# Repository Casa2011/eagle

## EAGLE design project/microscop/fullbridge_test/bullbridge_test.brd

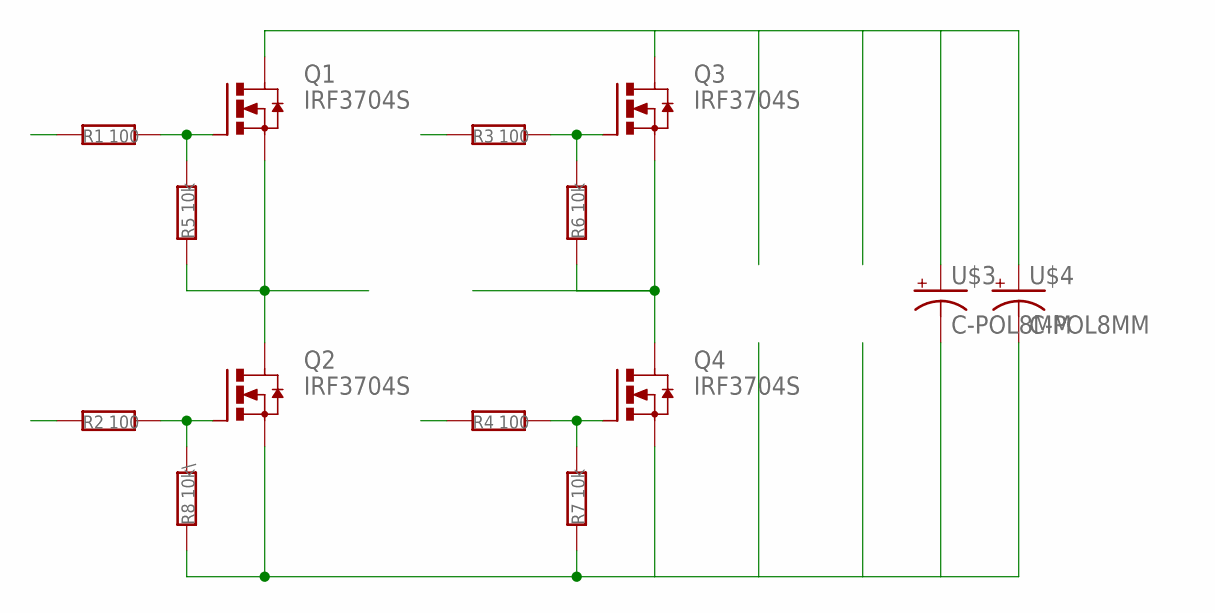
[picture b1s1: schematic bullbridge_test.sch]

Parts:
Q1, Q2, Q3, Q4: IRF3704S; D2PACK
R1, R2, R3, R4: 100; R0805
R5, R6, R7: 10k; R0805
R8: 10k\; R0805
U$3, U$4: C-POL8MM; PCAP8

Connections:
unnamed: Q1.1 (G), R1.2, R5.2
unnamed: Q3.1 (G), R3.2, R6.2
unnamed: Q4.1 (G), R4.2, R7.2
unnamed: Q1.3 (S), Q2.2 (D), R5.1
unnamed: Q3.3 (S), Q4.2 (D), R6.1
unnamed: Q1.2 (D), Q3.2 (D), U$3.P$1 (+), U$4.P$1 (+)
unnamed: Q2.1 (G), R2.2, R8.2
unnamed: Q2.3 (S), Q4.3 (S), R7.1, R8.1, U$3.P$2 (-), U$4.P$2 (-)

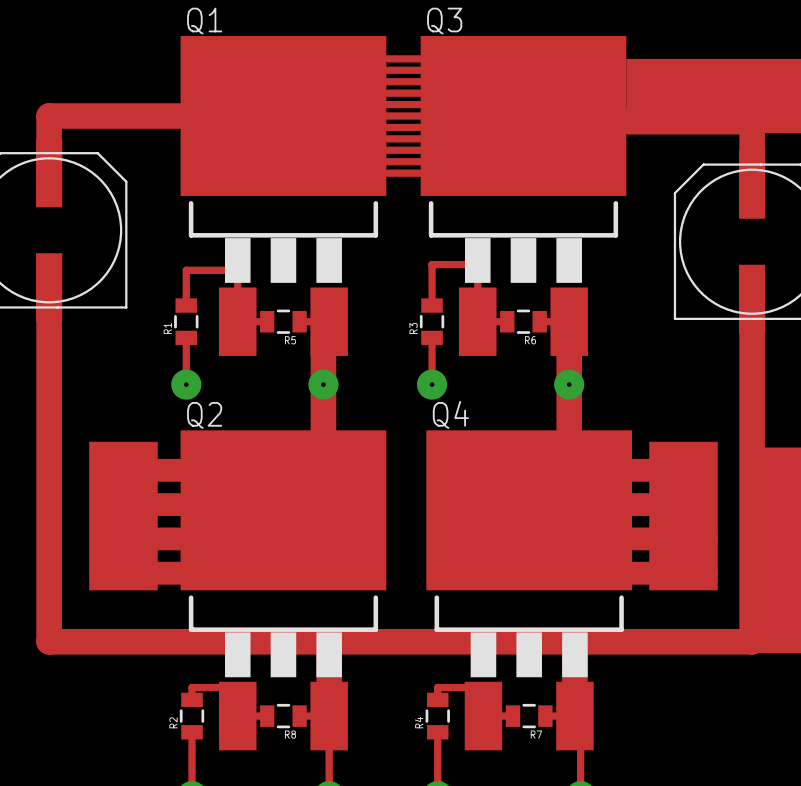
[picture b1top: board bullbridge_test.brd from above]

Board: 2 copper layers, 14 parts (0 on the bottom side), 8 nets.

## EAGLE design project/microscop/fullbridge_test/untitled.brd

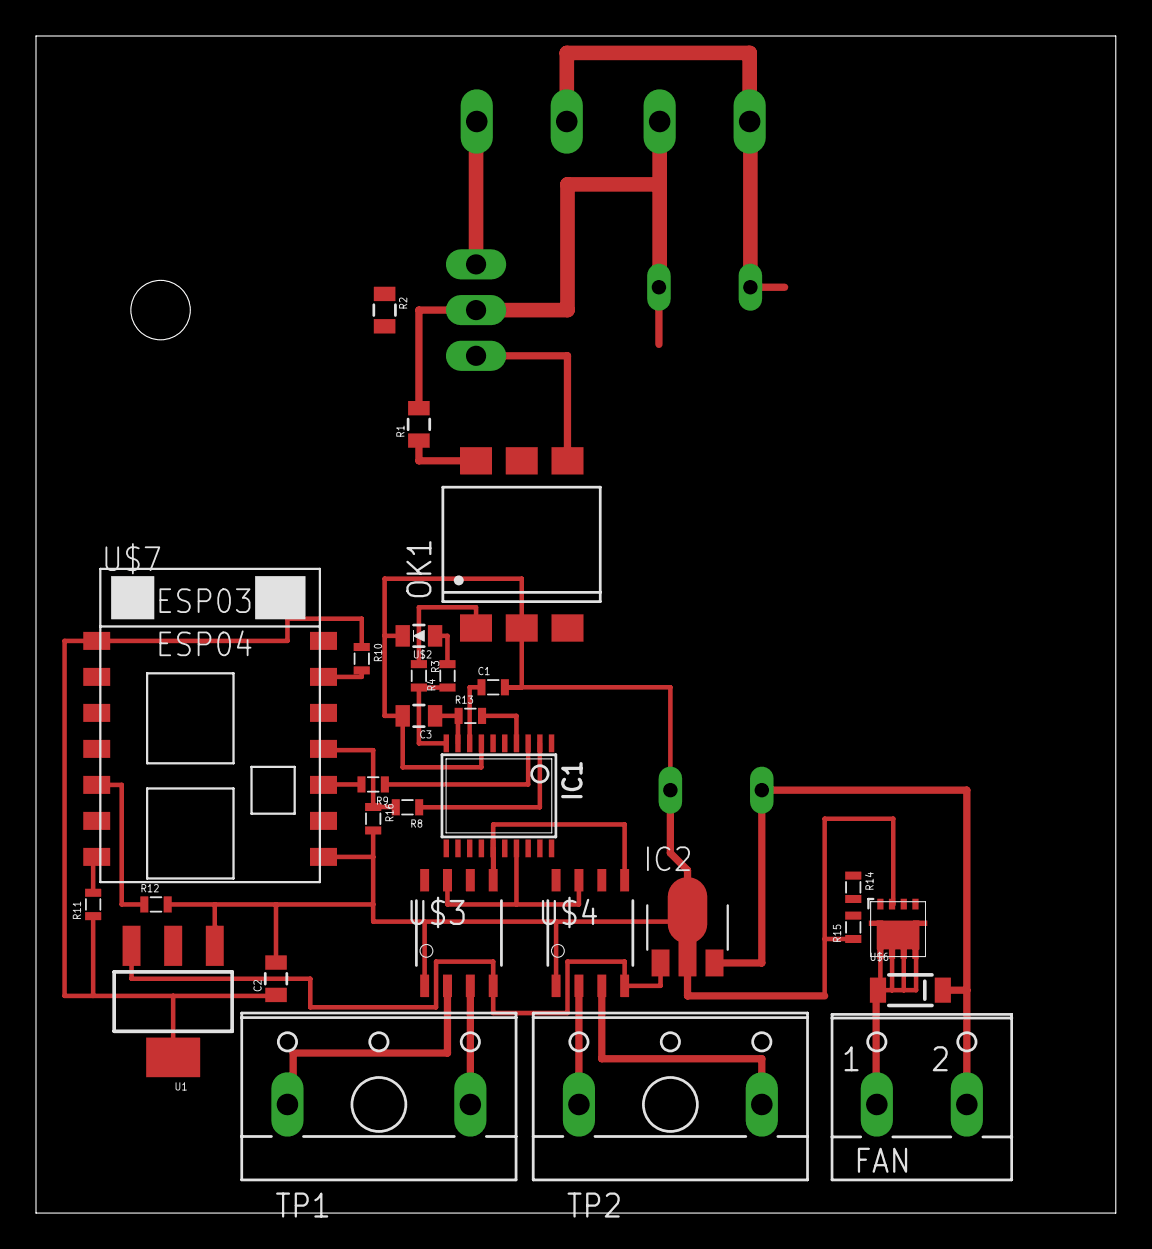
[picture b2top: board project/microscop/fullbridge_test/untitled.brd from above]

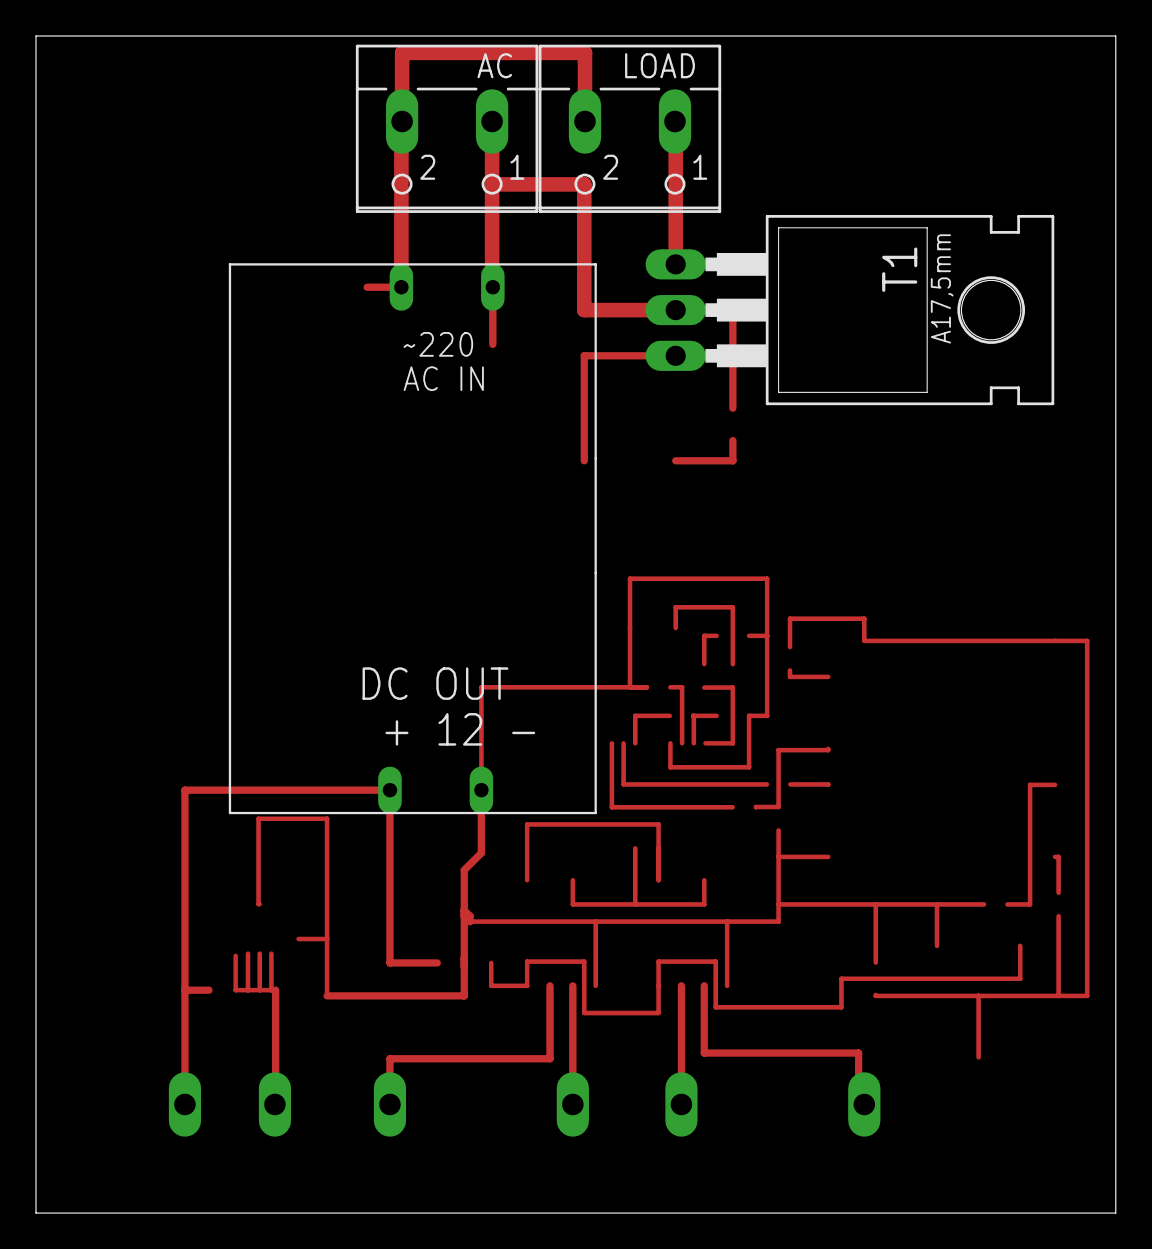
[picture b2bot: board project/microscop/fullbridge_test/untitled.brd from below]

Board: 2 copper layers, 60.0 x 65.4 mm, 33 parts (4 on the bottom side), 29 nets.

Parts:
AC: W237-102
C1: C0603
C2, C3: C0805
FAN: W237-102
IC1: STM8S003F3; TSSOP20
IC2: 78L05F; SOT89
LOAD: W237-102
OK1: MOC3043S; DIL6-SMD
R1, R2: 360; R0805
R3, R4: 1k; 0603
R8, R9, R10, R11, R12, R13, R14, R15, R16: 0603
T1: BT138-H; TO220BH
TP1, TP2: W237-2N
U1: SOT223
U$2: LED0805; 0805-LED
U$3, U$4: MAX6675; SO08
U$5: AON7200; DFN3X3
U$6: PMLL4150; SOD80C
U$7: ESP8266; ESP-03
U$8: AC-DC; ACDC12(1)

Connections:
12V: FAN.2, IC2.3, U$6.C, U$8.+12
+3V3: C2.1, R10.1, R11.1, U1.4, U$7.VCC
+5V: C3.1, IC1.9, IC2.1, R13.1, U1.3, U$3.4, U$4.4
DIMM_IN: IC1.10, R3.2, R4.1
ESP8266_!RST: R10.2, U$7.CH_PD
ESP8266_FLASH: R11.2, U$7.GPIO0
ESP8266_RX: IC1.2, R8.1
ESP8266_TX: IC1.3, R9.1
GND: C1.2, C2.2, C3.2, IC1.7, IC2.2, IC2.2@1, OK1.2, R12.2, R15.1, R16.2, U1.1, U$2.C, U$3.1, U$4.1, U$5.S:1, U$5.S:2, U$5.S:3, U$7.GND, U$8.GND
MAX7765_CLK: IC1.15, U$3.5, U$4.5
MAX7765_OUT: IC1.17, U$3.7, U$4.7
unnamed: TP1.2, U$3.3
unnamed: OK1.1, R3.1
unnamed: R4.2, U$2.A
unnamed: OK1.4, R2.2, T1.G
unnamed: OK1.6, R1.1
unnamed: AC.1, R1.2, T1.T2, U$8.P
unnamed: TP1.1, U$3.2
unnamed: AC.2, LOAD.2, U$8.N
unnamed: LOAD.1, R2.1, T1.T1
unnamed: TP2.2, U$4.3
unnamed: TP2.1, U$4.2
unnamed: R14.2, R15.2, U$5.G
unnamed: R8.2, R16.1, U$7.URXD
unnamed: R9.2, U$7.UTXD
unnamed: R12.1, U$7.GPIO15
unnamed: FAN.1, U$5.D, U$5.D:1, U$5.D:2, U$5.D:3, U$5.D:4, U$5.D:5, U$5.D:6, U$6.A
unnamed: C1.1, IC1.8
STM8_!RST: IC1.4, R13.2

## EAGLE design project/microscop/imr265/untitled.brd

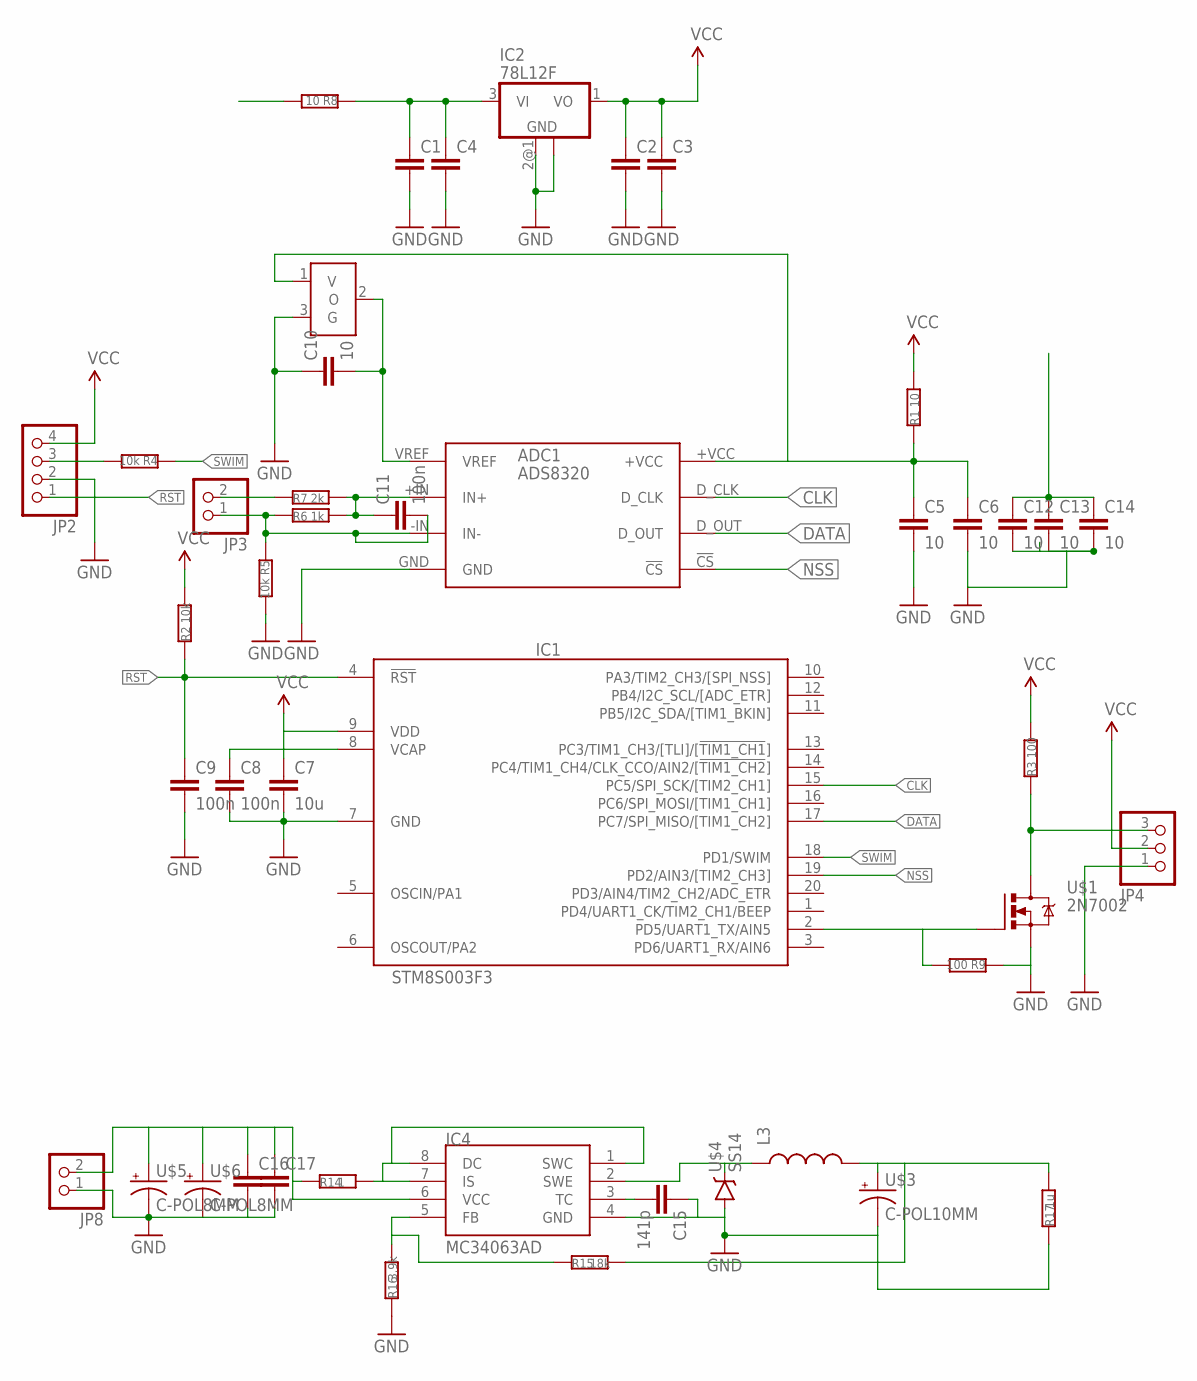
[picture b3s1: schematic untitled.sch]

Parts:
ADC1: ADS8320; S-PDSO-G8
C1, C2, C3, C4, C16, C17: CC0805; C0805
C5, C6, C10, C12, C13, C14: 10; C0805
C7: 10u; C0805
C8, C9, C11: 100n; C0603
C15: 141p; C0603
IC1: STM8S003F3; TSSOP20
IC2: 78L12F; SOT89
IC4: MC34063AD; SOIC8
JP2: PINHD-1X04_2.54; 1X04
JP3: PINHD-1X2; 1X02
JP4: PINHD-1X03_2.54; 1X03
JP8: PINHD-1X02_2.54; 1X02
L3: INDUCTORSRU1038; SRU1038
R1, R8: 10; 0603
R2, R4, R5: 10k; 0603
R3, R9: 100; 0603
R6: 1k; 0603
R7: 2k; 0603
R14: 1; R0805
R15: 18k; 0603
R16: 3.9k; 0603
R17: 1u; R0805
U$1: 2N7002; SOT23
U$2: REF3025; SOT23
U$3: C-POL10MM; PCAP10
U$4: SS14; SMA-DIODE
U$5, U$6: C-POL8MM; PCAP8

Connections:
CLK: ADC1.D_CLK, IC1.15 (PC5/SPI_SCK/[TIM2_CH1])
DATA: ADC1.D_OUT, IC1.17 (PC7/SPI_MISO/[TIM1_CH2])
GND: ADC1.GND, C1.2, C2.2, C3.2, C4.2, C5.2, C6.2, C7.2, C8.2, C9.2, C10.1, C12.2, C13.2, C14.2, C15.1, C16.2, C17.2, IC1.7 (GND), IC2.2 (GND), IC2.2@1 (GND), IC4.4 (GND), JP2.2, JP4.1, JP8.1, R5.2, R9.1, R16.1, R17.1, U$1.2 (S), U$2.3 (G), U$3.P$2 (-), U$4.A, U$5.P$2 (-), U$6.P$2 (-)
unnamed: ADC1.VREF, C10.2, U$2.2 (O)
unnamed: C1.1, C4.1, C12.1, C13.1, C14.1, IC2.3 (VI), L3.2, R8.1, R15.2, R17.2, U$3.P$1 (+)
unnamed: ADC1.+VCC, C5.1, C6.1, R1.1, U$2.1 (V)
unnamed: C8.1, IC1.8 (VCAP)
unnamed: IC1.2 (PD5/UART1_TX/AIN5), R9.2, U$1.1 (G)
unnamed: JP4.3, R3.1, U$1.3 (D)
unnamed: C16.1, C17.1, IC4.6 (VCC), JP8.2, R14.1, U$5.P$1 (+), U$6.P$1 (+)
unnamed: ADC1.-IN (IN-), C11.2, JP3.1, R5.1, R6.1
unnamed: ADC1.+IN (IN+), C11.1, R6.2, R7.2
unnamed: JP3.2, R7.1
unnamed: C15.2, IC4.3 (TC)
unnamed: IC4.2 (SWE), L3.1, U$4.C
unnamed: IC4.5 (FB), R15.1, R16.2
unnamed: IC4.1 (SWC), IC4.7 (IS), IC4.8 (DC), R14.2
NSS: ADC1.!CS, IC1.19 (PD2/AIN3/[TIM2_CH3])
RST: C9.1, IC1.4 (!RST), JP2.1, R2.1
SWIM: IC1.18 (PD1/SWIM), R4.1
SWIMR: JP2.3, R4.2
VCC: C2.1, C3.1, C7.1, IC1.9 (VDD), IC2.1 (VO), JP2.4, JP4.2, R1.2, R2.2, R3.2

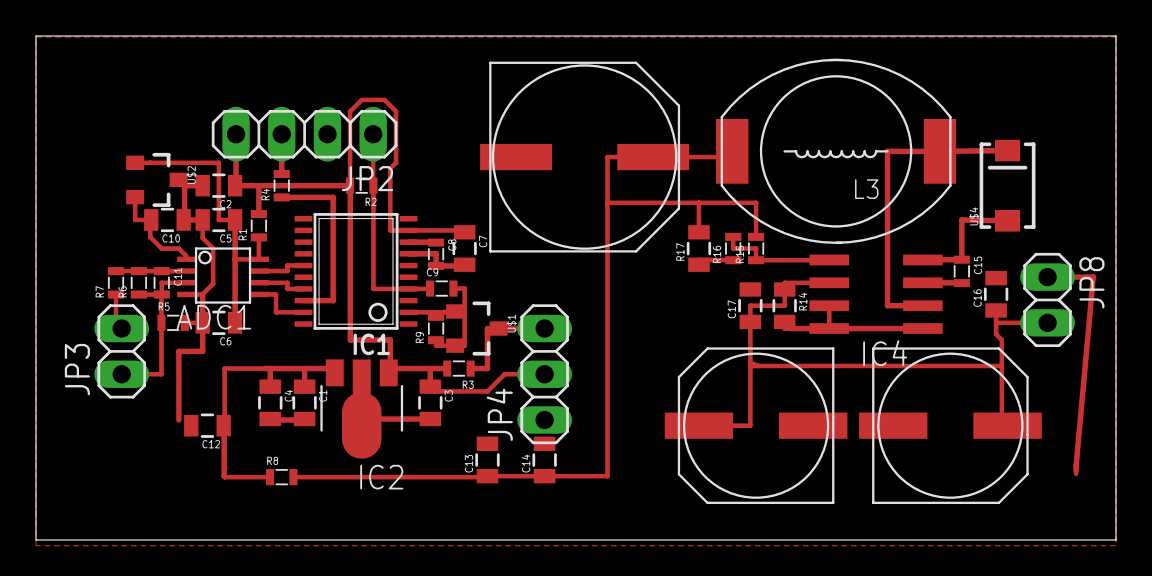
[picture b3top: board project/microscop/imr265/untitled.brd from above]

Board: 2 copper layers, 60.0 x 28.0 mm, 45 parts (0 on the bottom side), 22 nets.

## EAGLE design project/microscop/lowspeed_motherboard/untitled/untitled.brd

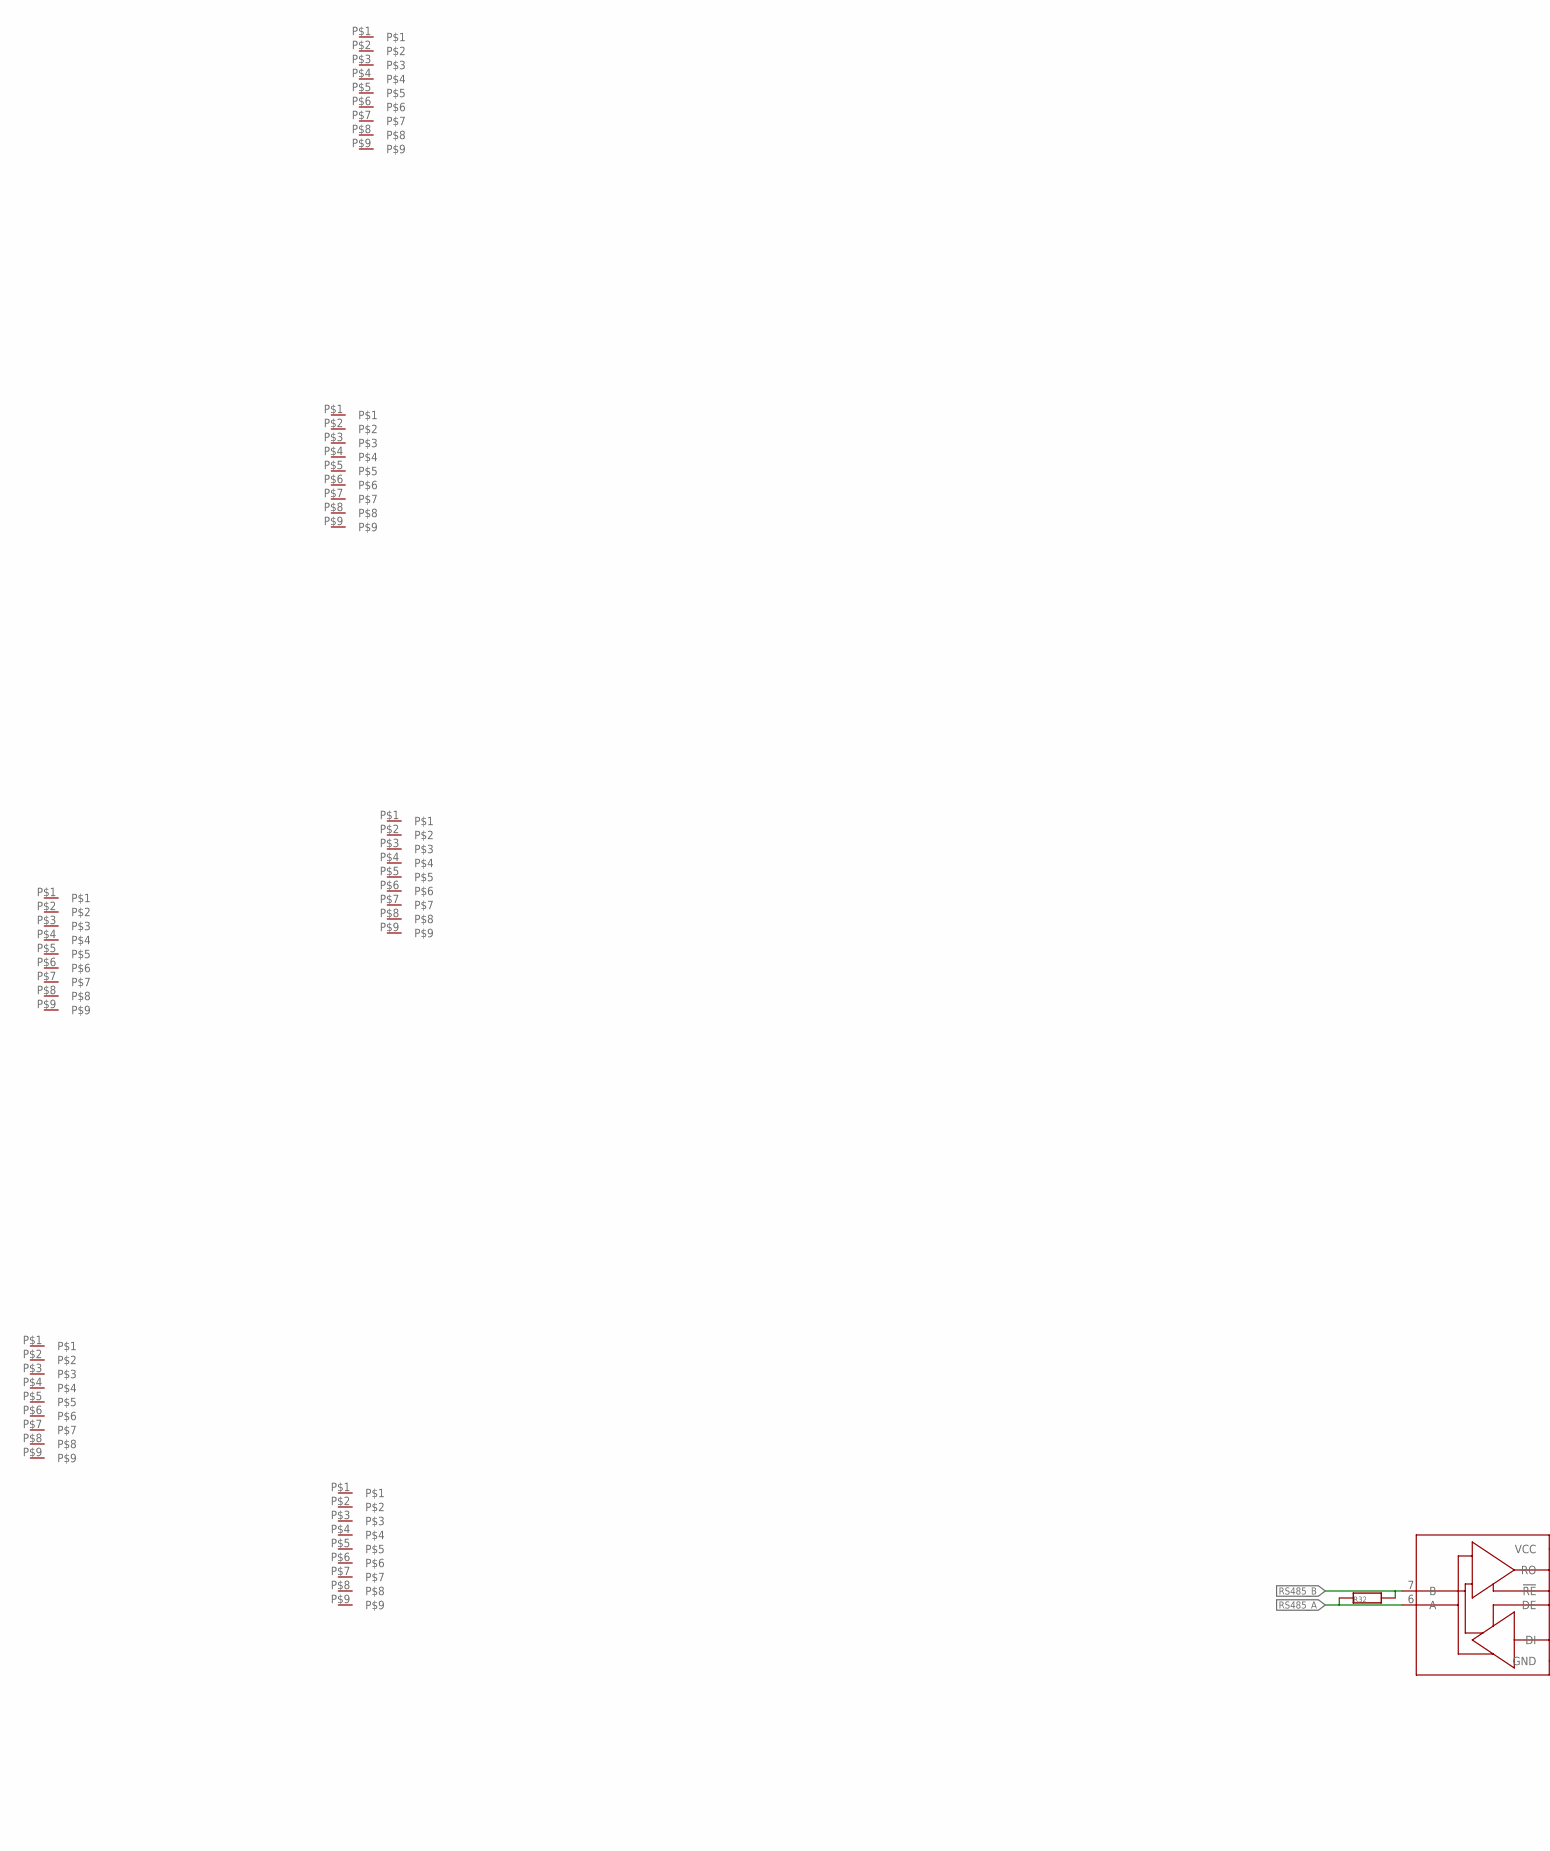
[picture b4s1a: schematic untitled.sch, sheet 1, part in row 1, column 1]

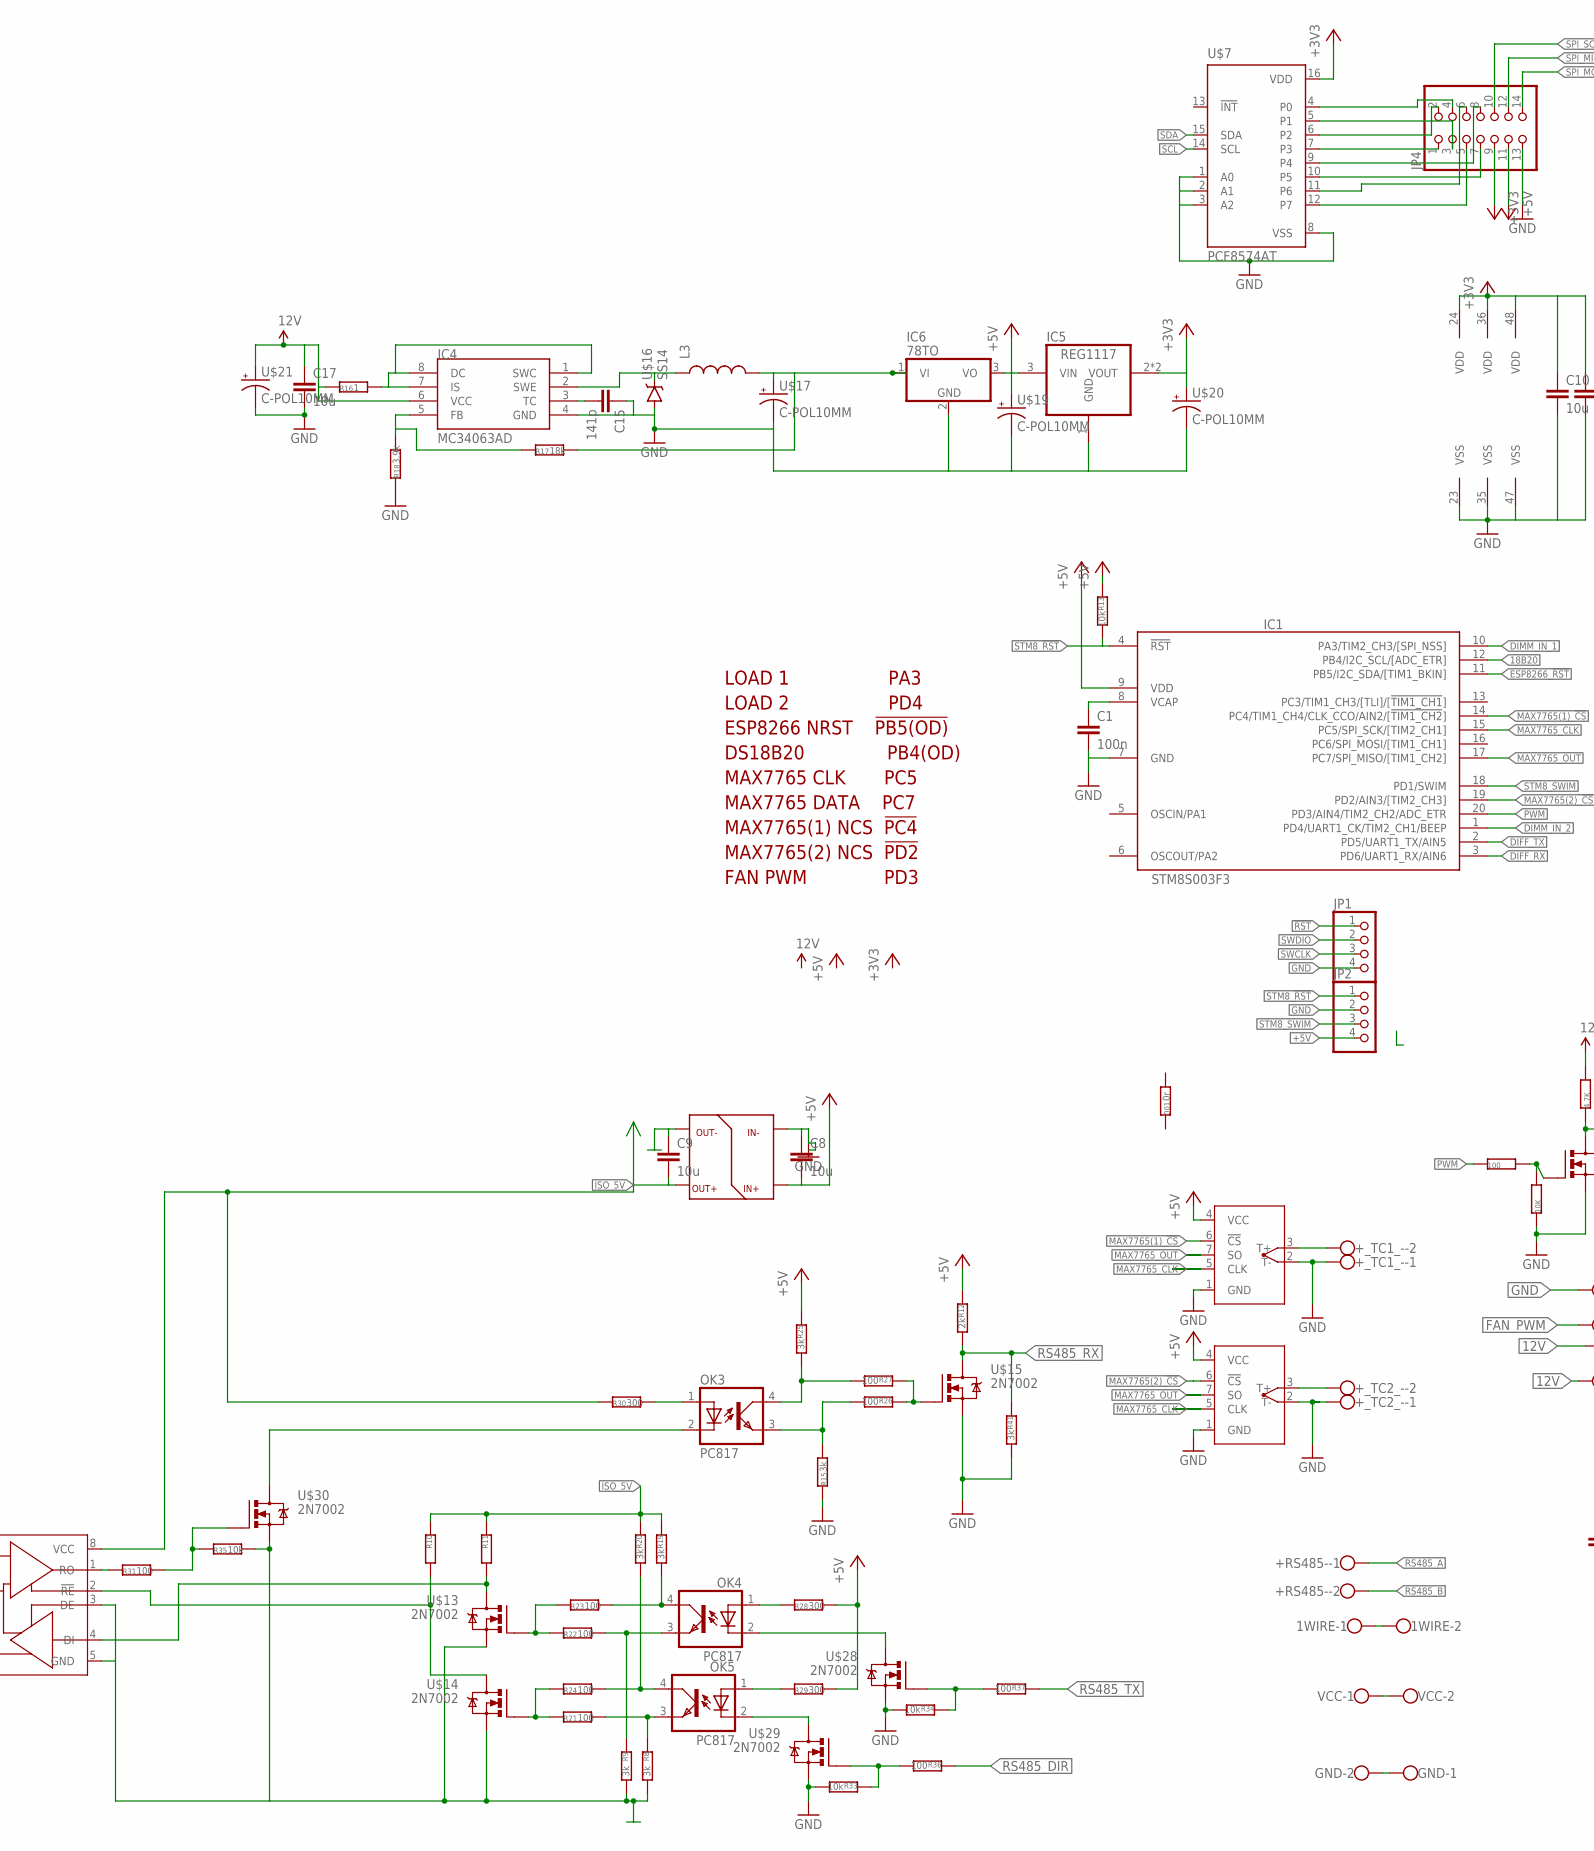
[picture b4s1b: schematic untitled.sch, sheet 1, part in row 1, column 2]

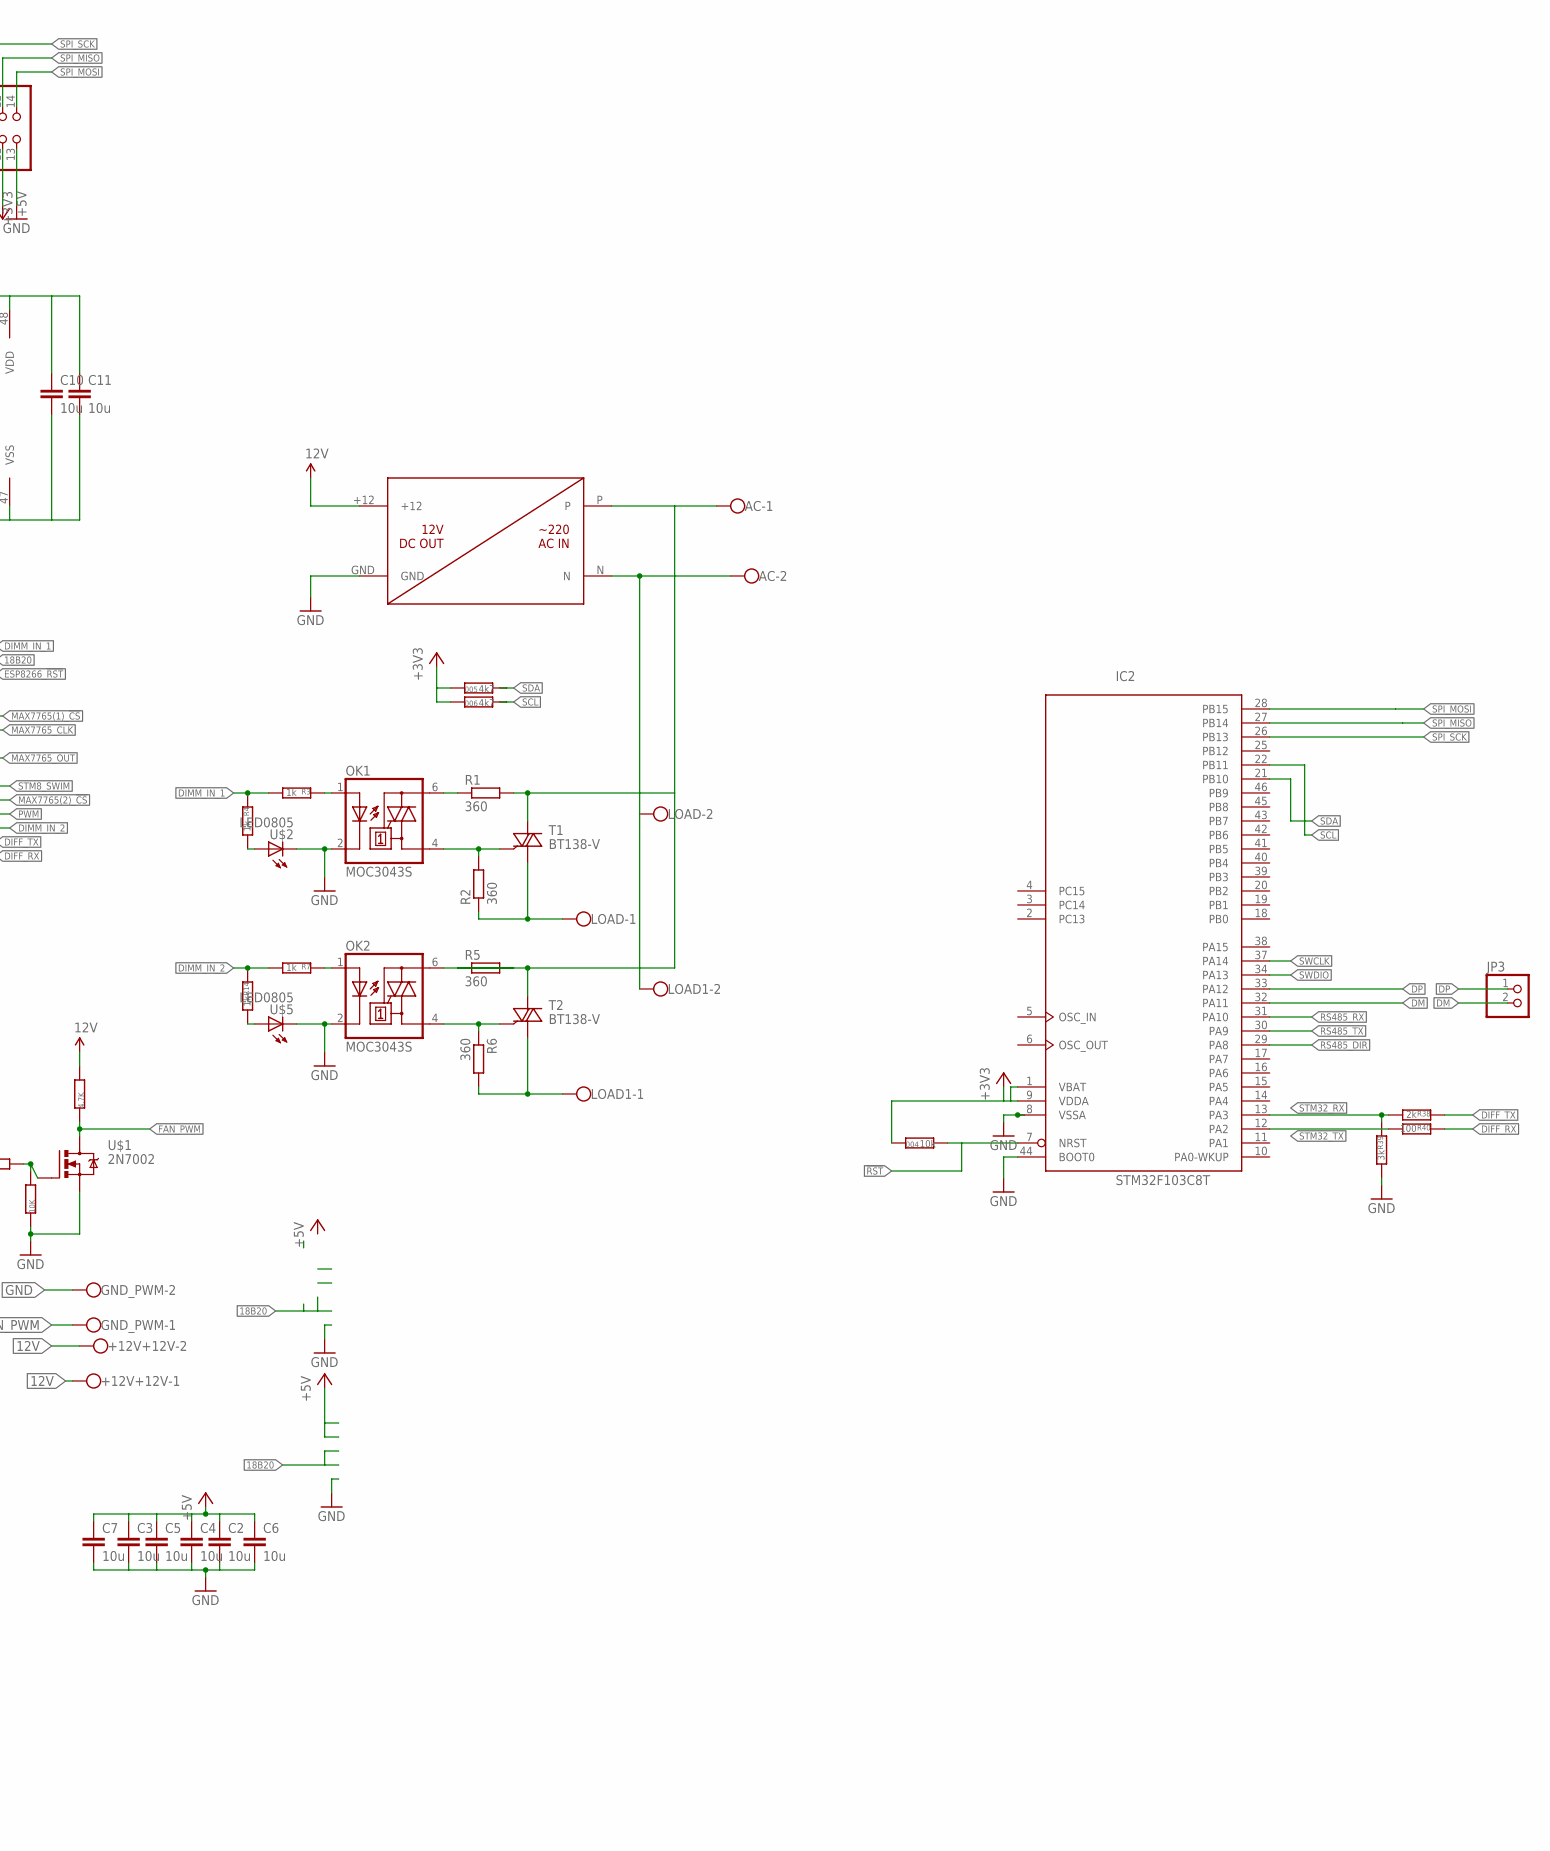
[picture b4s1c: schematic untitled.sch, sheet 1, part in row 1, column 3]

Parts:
001: 0r; 0603
1WIRE: W237-102
004: 10k; 0603
4.7K, 10K, 100: R0603; 0603
005, 006: 4k7; 0603
+12V+12V: W237-102
+RS485-: W237-102
+_TC1_-, +_TC2_-: W237-102
AC: W237-102
C1: 100n; C0603
C2, C3, C4, C5, C6, C7, C8, C9, C17: 10u; C0805
C10, C11: 10u; C0603
C15: 141p; C0603
GND: W237-102
GND_PWM: W237-102
IC1: STM8S003F3; TSSOP20
IC2: STM32F103C8T; LQFP48
IC4: MC34063AD; SOIC8
IC5: REG1117; SOT223
IC6: 78TO; D2PACK
JP1, JP2: PINHD-1X4; 1X04
JP3: PINHD-1X02_2.00; 1X02M
JP4: PINHD-2X07_2.54-SMD; 2X07SMD
L3: INDUCTORSRU1038; SRU1038
LOAD, LOAD1: W237-102
OK1, OK2: MOC3043S; DIL6-SMD
OK3, OK4, OK5: PC817; DIL4-SMD
R1, R2, R5, R6: 360; 0207/5V
R3, R4, R7, R14: 1k; 0603
R8, R9, R15, R19, R20, R25, R39, R41: 3k; 0603
R10, R11: R0603; 0603
R12, R38: 2k; 0603
R13, R33, R34, R35: 10k; 0603
R16: 1; R0805
R17: 18k; 0603
R18: 3.9k; 0603
R21, R22, R23, R24, R26, R27, R31, R36, R37, R40: 100; 0603
R28, R29, R30: 300; 0603
R32: R0805
T1, T2: BT138-V; TO220BV
U$1, U$13, U$14, U$15, U$28, U$29, U$30: 2N7002; SOT23
U$2, U$5: LED0805; 0805-LED
U$3, U$6: MAX6675; SO08
U$4: ADM1485; SO08
U$7: PCF8574AT; SO16L
U$8: AC-DC; ACDC12(1)
U$12: DCDC5050; DCDC/0505
U$16: SS14; SMA-DIODE
U$17, U$19, U$20, U$21: C-POL10MM; PCAP10
U$22, U$23, U$24, U$25, U$26, U$27: D9MG
VCC: W237-102

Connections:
12V: 4.7K.2, +12V+12V.1, +12V+12V.2, C17.1, IC4.6 (VCC), R16.1, U$8.+12, U$21.P$1 (+)
18B20: 1WIRE.1, 1WIRE.2, IC1.12 (PB4/I2C_SCL/[ADC_ETR])
!RST: 004.2, IC2.7 (NRST), JP1.1
+3V3: 004.1, 005.1, 006.1, C10.1, C11.1, IC2.1 (VBAT), IC2.9 (VDDA), IC2.24 (VDD), IC2.36 (VDD), IC2.48 (VDD), IC5.2 (VOUT), IC5.4 (VOUT), JP4.9, U$7.16 (VDD), U$20.P$1 (+)
+5V: C2.1, C3.1, C4.1, C5.1, C6.1, C7.1, C8.2, IC1.9 (VDD), IC5.3 (VIN), IC6.3 (VO), JP2.4, JP4.11, R12.1, R13.1, R25.1, R28.2, R29.2, U$3.4 (VCC), U$6.4 (VCC), U$12.P$2 (IN+), U$19.P$1 (+), VCC.1, VCC.2
+7V: IC6.1 (VI), L3.2, R17.2, U$17.P$1 (+)
DIFF_RX: IC1.3 (PD6/UART1_RX/AIN6), R40.1
DIFF_TX: IC1.2 (PD5/UART1_TX/AIN5), R38.1
DIMM_IN_1: IC1.10 (PA3/TIM2_CH3/[SPI_NSS]), R3.2, R4.1
DIMM_IN_2: IC1.1 (PD4/UART1_CK/TIM2_CH1/BEEP), R7.2, R14.1
DM: IC2.32 (PA11), JP3.2
DP: IC2.33 (PA12), JP3.1
ESP8266_!RST: IC1.11 (PB5/I2C_SDA/[TIM1_BKIN])
FAN_PWM: 4.7K.1, GND_PWM.1, U$1.3 (D)
GND: 10K.1, +_TC1_-.1, +_TC2_-.1, C1.2, C2.2, C3.2, C4.2, C5.2, C6.2, C7.2, C8.1, C10.2, C11.2, C15.1, C17.2, GND.1, GND.2, GND_PWM.2, IC1.7 (GND), IC2.8 (VSSA), IC2.23 (VSS), IC2.35 (VSS), IC2.44 (BOOT0), IC2.47 (VSS), IC4.4 (GND), IC5.1 (GND), IC6.2 (GND), JP1.4, JP2.2, JP4.13, OK1.2 (C), OK2.2 (C), R15.1, R18.1, R33.2, R34.2, R39.2, R41.2, U$1.2 (S), U$2.C, U$3.1 (GND), U$3.2 (T-), U$5.C, U$6.1 (GND), U$6.2 (T-), U$7.1 (A0), U$7.2 (A1), U$7.3 (A2), U$7.8 (VSS), U$8.GND, U$12.P$1 (IN-), U$15.2 (S), U$16.A, U$17.P$2 (-), U$19.P$2 (-), U$20.P$2 (-), U$21.P$2 (-), U$28.2 (S), U$29.2 (S)
ISO_5V: C9.2, R10.1, R11.1, R19.1, R20.1, R30.1, U$4.8 (VCC), U$12.P$5 (OUT+)
ISO_GND: C9.1, R8.2, R9.2, R35.2, U$4.3 (DE), U$4.5 (GND), U$12.P$4 (OUT-), U$13.2 (S), U$14.2 (S), U$30.2 (S)
MAX7765(1)_!CS: IC1.14 (PC4/TIM1_CH4/CLK_CCO/AIN2/[!TIM1_CH2!]), U$3.6 (!CS)
MAX7765(2)_!CS: IC1.19 (PD2/AIN3/[TIM2_CH3]), U$6.6 (!CS)
MAX7765_CLK: IC1.15 (PC5/SPI_SCK/[TIM2_CH1]), U$3.5 (CLK), U$6.5 (CLK)
MAX7765_OUT: IC1.17 (PC7/SPI_MISO/[TIM1_CH2]), U$3.7 (SO), U$6.7 (SO)
unnamed: +_TC1_-.2, U$3.3 (T+)
unnamed: OK1.1 (A), R3.1
unnamed: R4.2, U$2.A
unnamed: 10K.2, 100.2, U$1.1 (G)
unnamed: JP4.4, U$7.4 (P0)
unnamed: OK1.4 (A1), R2.2, T1.G
unnamed: OK1.6 (A2), R1.1
unnamed: +_TC2_-.2, U$6.3 (T+)
unnamed: AC.2, LOAD.2, LOAD1.2, U$8.N
unnamed: LOAD.1, R2.1, T1.T1 (A1)
unnamed: OK2.4 (A1), R6.1, T2.G
unnamed: OK2.6 (A2), R5.2
unnamed: JP4.3, U$7.5 (P1)
unnamed: JP4.2, U$7.6 (P2)
unnamed: JP4.1, U$7.7 (P3)
unnamed: JP4.8, U$7.9 (P4)
unnamed: JP4.7, U$7.10 (P5)
unnamed: JP4.6, U$7.11 (P6)
unnamed: JP4.5, U$7.12 (P7)
unnamed: OK4.3 (EMIT), R9.1, R22.2
unnamed: AC.1, R1.2, R5.1, T1.T2 (A2), T2.T2 (A2), U$8.P
unnamed: OK5.3 (EMIT), R8.1, R21.2
unnamed: C1.1, IC1.8 (VCAP)
unnamed: LOAD1.1, R6.2, T2.T1 (A1)
unnamed: OK2.1 (A), R7.1
unnamed: R14.2, U$5.A
unnamed: R10.2, U$4.2 (!RE), U$14.3 (D)
unnamed: R11.2, U$4.4 (DI), U$13.3 (D)
unnamed: OK3.4 (COL), R25.2, R27.2
unnamed: OK3.3 (EMIT), R15.2, R26.2
unnamed: C15.2, IC4.3 (TC)
unnamed: IC4.2 (SWE), L3.1, U$16.C
unnamed: IC4.5 (FB), R17.1, R18.2
unnamed: IC4.1 (SWC), IC4.7 (IS), IC4.8 (DC), R16.2
unnamed: OK5.4 (COL), R20.2, R24.2
unnamed: OK4.4 (COL), R19.2, R23.2
unnamed: R22.1, R23.1, U$13.1 (G)
unnamed: R21.1, R24.1, U$14.1 (G)
unnamed: R26.1, R27.1, U$15.1 (G)
unnamed: OK4.2 (C), U$28.3 (D)
unnamed: OK3.1 (A), R30.2
unnamed: OK3.2 (C), U$30.3 (D)
unnamed: OK4.1 (A), R28.1
unnamed: R31.1, U$4.1 (RO)
unnamed: OK5.1 (A), R29.1
unnamed: OK5.2 (C), U$29.3 (D)
unnamed: R31.2, R35.1, U$30.1 (G)
PWM: 100.1, IC1.20 (PD3/AIN4/TIM2_CH2/ADC_ETR)
RS485_A: +RS485-.1, R32.1, U$4.6 (A)
RS485_B: +RS485-.2, R32.2, U$4.7 (B)
RS485_DIR: IC2.29 (PA8), R36.1
RS485_RX: IC2.31 (PA10), R12.2, R41.1, U$15.3 (D)
RS485_TX: IC2.30 (PA9), R37.1
SCL: 006.2, IC2.22 (PB11), U$7.14 (SCL)
SDA: 005.2, IC2.21 (PB10), U$7.15 (SDA)
SPI_MISO: IC2.27 (PB14), JP4.12
SPI_MOSI: IC2.28 (PB15), JP4.14
SPI_SCK: IC2.26 (PB13), JP4.10
STM8_!RST: IC1.4 (!RST), JP2.1, R13.2
STM8_SWIM: IC1.18 (PD1/SWIM), JP2.3
STM32_RX: IC2.13 (PA3), R38.2, R39.1
STM32_TX: IC2.12 (PA2), R40.2
SWCLK: IC2.37 (PA14), JP1.3
SWDIO: IC2.34 (PA13), JP1.2
~RS485_DIR: R33.1, R36.2, U$29.1 (G)
~RS485_TX: R34.1, R37.2, U$28.1 (G)

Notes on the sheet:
LOAD 1 PA3 LOAD 2 PD4 ESP8266 NRST !PB5(OD) DS18B20 PB4(OD) MAX7765 CLK PC5 MAX7765 DATA PC7 MAX7765(1) NCS !PC4 MAX7765(2) NCS !PD2 FAN PWM PD3

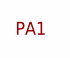
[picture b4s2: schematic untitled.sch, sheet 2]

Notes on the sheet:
PA1

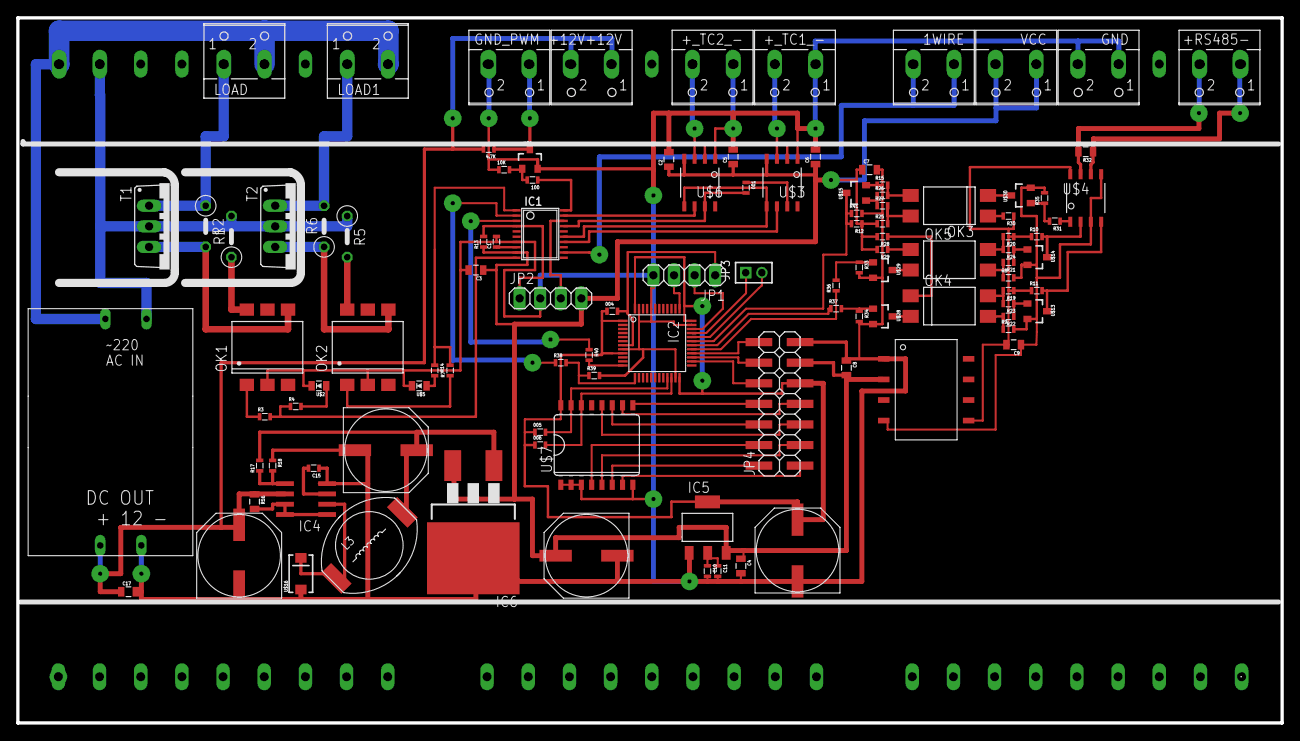
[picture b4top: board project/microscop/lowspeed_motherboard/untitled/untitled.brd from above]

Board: 2 copper layers, 156.0 x 87.0 mm, 117 parts (1 on the bottom side), 86 nets.

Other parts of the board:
U$9, U$10: HEATSINK

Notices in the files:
parts and their libraries:
SparkFun-Passives: Licensing: Creative Commons ShareAlike 4.0 International - https://creativecommons.org/licenses/by-sa/4.0
